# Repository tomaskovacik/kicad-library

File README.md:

schematics parts and PCB footprints for kicad

S3860M-S bluetooth audio module based on OVC3860

XS3886 bluetooth audio module based on OVC3860

MB-CM15113 bluetooth audio module

F-3188 CSR8645 based bluetooth 4.0 module

BLK-MD-SPK-B bluetooth audio module based on OVC3860

68HC05 motorola cpu

SOYO-BT24G03 bluetooth module

aimtec DC-DC convertor AM1D 

F-6888 - BK3254 BT4.0 audio bluetooth module 

Microchip BM20 and BM23 BT modules

F-6188 - BK8000L BT2.0 audio bluetooth module 

MAX809-810 

various 3.5mm jacks

MC33660 

bluepill (stm32F103C)

LM2594

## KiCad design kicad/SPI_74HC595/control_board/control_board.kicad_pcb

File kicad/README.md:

schematics and PCBs made in kicad

- vwcdpic: based on work from www.k9spud.com, remake of PCB, my own tests

arduino_atmega88: single side PCB for arduino based on atmega88 (cheap on ebay ;)

arduino_based_cdc_emulator: PCBs for arduino based CD changer emulator for audi HU

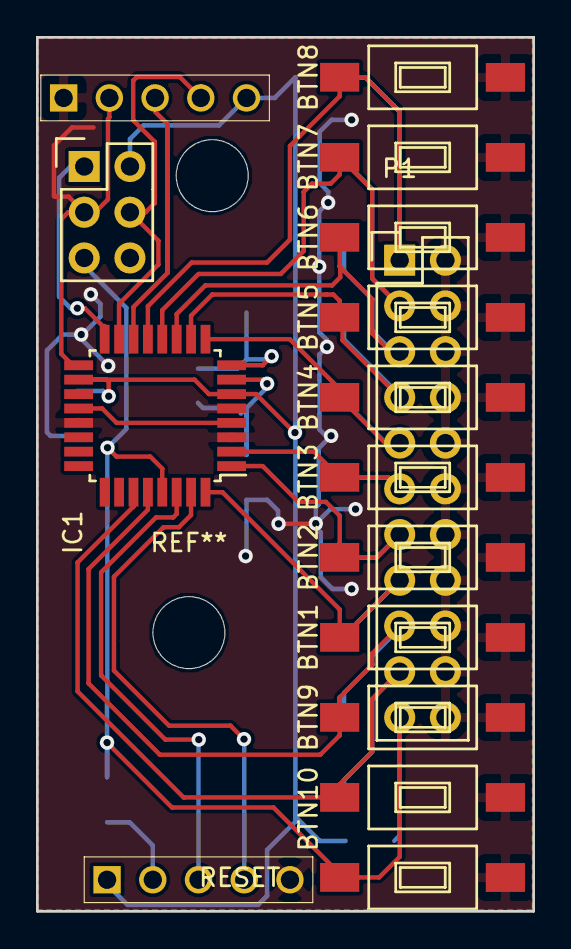
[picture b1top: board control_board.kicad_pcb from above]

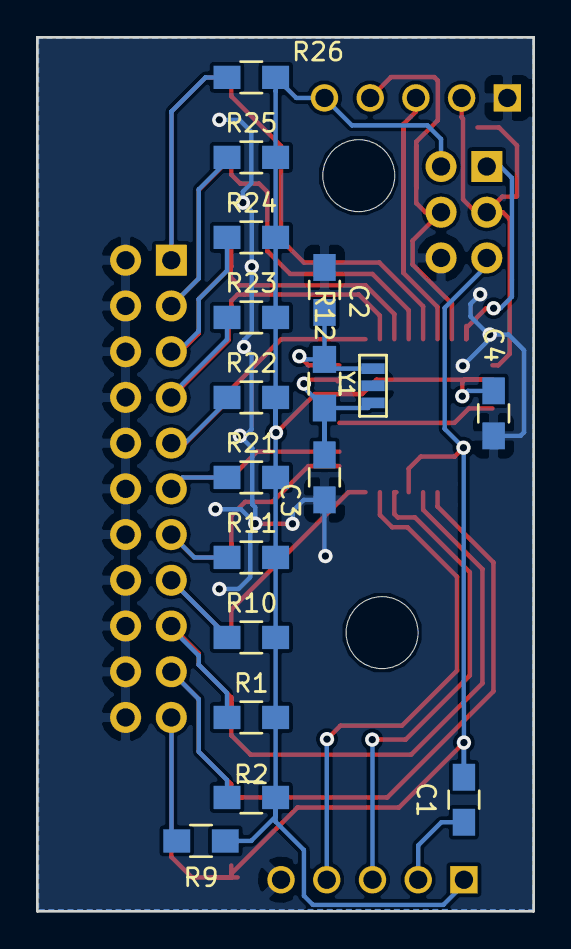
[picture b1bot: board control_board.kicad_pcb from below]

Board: 2 copper layers, 27.6 x 48.6 mm, 33 parts (17 on the bottom side), 22 nets.

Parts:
BTN1, BTN2, BTN3, BTN4, BTN5, BTN6, BTN7, BTN8, BTN9, BTN10: SW_PUSH; SW_SPST_FSMSM
C1, C4: 100n; C_0805_HandSoldering
C2, C3: 22p; C_0805_HandSoldering
IC1: ATMEGA328-A; TQFP-32_7x7mm_Pitch0.8mm
P1: CONN_02X11; Pin_Header_Straight_2x11
P6, P12: CONN_01X05; pin_array_5x1
P10: CONN_02X03; Pin_Header_Straight_2x03
R1, R2, R9, R10, R11, R21, R22, R23, R24, R25, R26: 10k; R_0805_HandSoldering
R12: 1M; R_0805_HandSoldering
RESET: SW_PUSH; SW_SPST_FSMSM
Y1: 16Mhz; MURATA_CSTCE_V53

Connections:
/BTN1: BTN1.1, IC1.32, P1.15, R10.2
/BTN2: BTN2.1, IC1.1, P1.13, R11.2
/BTN3: BTN3.1, IC1.2, P1.11, R21.2
/BTN4: BTN4.1, IC1.9, P1.9, R22.2
/BTN5: BTN5.1, IC1.10, P1.7, R23.2
/BTN6: BTN6.1, IC1.11, P1.5, R24.2
/BTN7: BTN7.1, IC1.12, P1.3, R25.2
/BTN8: BTN8.1, IC1.13, P1.1, R26.2
/BTN9: BTN9.1, IC1.28, P1.17, R1.2
/BTN10: BTN10.1, IC1.27, P1.19, R2.2
/LATCH: IC1.14, P12.3
/MISO: IC1.16, P10.1
/MOSI: IC1.15, P10.4, P12.4
/RESET: C1.2, IC1.29, P1.21, P10.5, R9.2, RESET.1
/RX: IC1.30, P6.3
/SCK: IC1.17, P10.3, P12.2
/TX: IC1.31, P6.4
GND: BTN1.2, BTN2.2, BTN3.2, BTN4.2, BTN5.2, BTN6.2, BTN7.2, BTN8.2, BTN9.2, BTN10.2, C2.2, C3.2, C4.2, IC1.3, IC1.5, IC1.21, P1.2, P1.4, P1.6, P1.8, P1.10, P1.12, P1.14, P1.16, P1.18, P1.20, P1.22, P6.5, P10.6, P12.1, RESET.2, Y1.3
unnamed: C1.1, P6.2
unnamed: C2.1, IC1.8, R12.2, Y1.1
unnamed: C3.1, IC1.7, R12.1, Y1.2
VCC: C4.1, IC1.4, IC1.6, IC1.18, IC1.20, P6.1, P10.2, P12.5, R1.1, R2.1, R9.1, R10.1, R11.1, R21.1, R22.1, R23.1, R24.1, R25.1, R26.1

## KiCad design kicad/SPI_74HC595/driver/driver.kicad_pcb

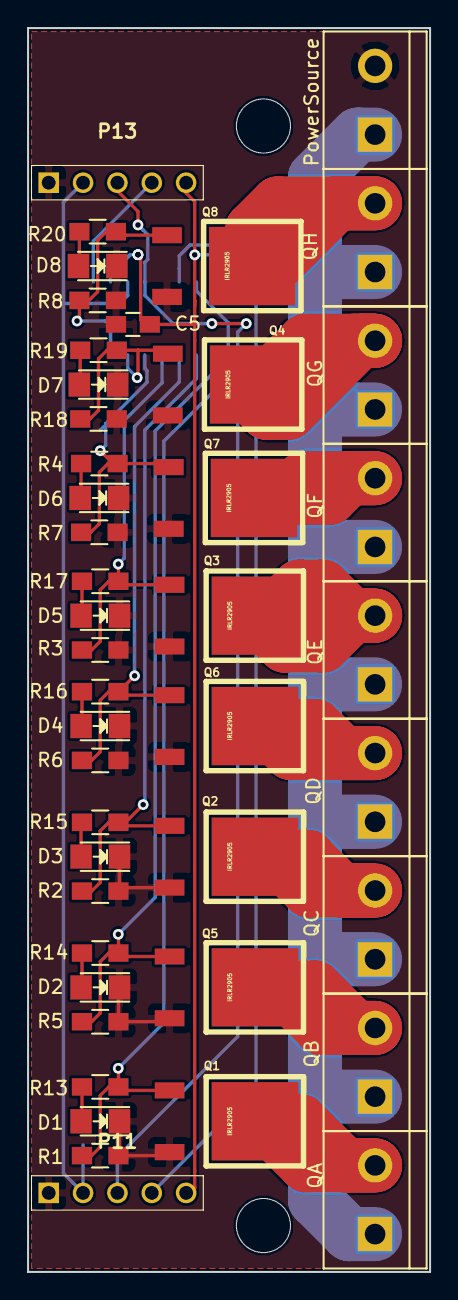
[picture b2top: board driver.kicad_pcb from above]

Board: 2 copper layers, 29.7 x 91.9 mm, 45 parts (1 on the bottom side), 31 nets.

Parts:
C5: 100n; C_0805_HandSoldering
D1, D2, D3, D4, D5, D6, D7, D8: LED; LED_1206
P11, P13: CONN_01X05; pin_array_5x1
PowerSource: CONN_01X02; bornier2
Q1, Q2, Q3, Q4, Q5, Q6, Q7, Q8: IRLR2905; TO-252-3
QA: CONN_01X02; bornier2
QB: CONN_01X02; bornier2
QC: CONN_01X02; bornier2
QD: CONN_01X02; bornier2
QE: CONN_01X02; bornier2
QF: CONN_01X02; bornier2
QG: CONN_01X02; bornier2
QH: CONN_01X02; bornier2
R1, R2, R3, R4, R5, R6, R7, R8: 10k; R_0805_HandSoldering
R13, R14, R15, R16, R17, R18, R19, R20: 470; R_0805_HandSoldering
U1: 74HC595; SOIC-16_3.9x9.9mm_Pitch1.27mm

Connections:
+12V: PowerSource.1, QA.1, QB.1, QC.1, QD.1, QE.1, QF.1, QG.1, QH.1
/LATCH: P11.3, P13.3, U1.12
/MOSI: P11.4, U1.14
/OUT: P13.4, U1.9
/QA: Q1.1, R1.2, R13.2, U1.15
/QB: Q5.1, R5.2, R14.2, U1.1
/QC: Q2.1, R2.2, R15.2, U1.2
/QD: Q6.1, R6.2, R16.2, U1.3
/QE: Q3.1, R3.2, R17.2, U1.4
/QF: Q7.1, R7.2, R18.2, U1.5
/QG: Q4.1, R4.2, R19.2, U1.6
/QH: Q8.1, R8.2, R20.2, U1.7
/SCK: P11.2, P13.2, U1.11
GND: C5.2, D1.1, D2.1, D3.1, D4.1, D5.1, D6.1, D7.1, D8.1, P11.1, P13.1, PowerSource.2, Q1.2, Q2.2, Q3.2, Q4.2, Q5.2, Q6.2, Q7.2, Q8.2, R1.1, R2.1, R3.1, R4.1, R5.1, R6.1, R7.1, R8.1, U1.8, U1.13
unnamed: D1.2, R13.1
unnamed: D2.2, R14.1
unnamed: D3.2, R15.1
unnamed: D4.2, R16.1
unnamed: D5.2, R17.1
unnamed: D6.2, R18.1
unnamed: D7.2, R19.1
unnamed: D8.2, R20.1
unnamed: Q1.3, QA.2
unnamed: Q2.3, QC.2
unnamed: Q3.3, QE.2
unnamed: Q4.3, QG.2
unnamed: Q5.3, QB.2
unnamed: Q6.3, QD.2
unnamed: Q7.3, QF.2
unnamed: Q8.3, QH.2
VCC: C5.1, P11.5, P13.5, U1.10, U1.16

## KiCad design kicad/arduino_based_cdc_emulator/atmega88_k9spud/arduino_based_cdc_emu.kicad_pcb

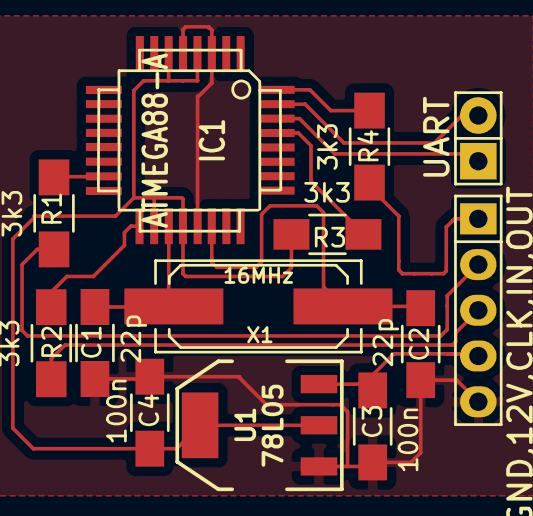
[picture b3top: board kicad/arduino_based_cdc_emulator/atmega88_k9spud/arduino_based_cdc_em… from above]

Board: 2 copper layers, 13 parts (0 on the bottom side), 14 nets.

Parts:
C1, C2: 22p; C_1206_HandSoldering
C3, C4: 100n; C_1206_HandSoldering
GND,12V,CLK,IN,OUT: CONN_5; Pin_Header_Straight_1x05
IC1: ATMEGA88-A; TQFP-32
R1, R2, R3, R4: 3k3; R_1206_HandSoldering
U1: 78L05; SOT-223-REGULATOR
UART: CONN_2; Pin_Header_Straight_1x02
X1: 16MHz; Q_49U3HMS

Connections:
+5V: C4.1, IC1.4, IC1.6, IC1.18, IC1.20, R3.2, U1.VO
+12V: C3.1, GND,12V,CLK,IN,OUT.4, U1.VI
/Clock: GND,12V,CLK,IN,OUT.3, R2.2
/DataIn: GND,12V,CLK,IN,OUT.2, R1.2
/DataOut: GND,12V,CLK,IN,OUT.1, R4.2
GND: C1.1, C2.1, C3.2, C4.2, GND,12V,CLK,IN,OUT.5, IC1.3, IC1.5, IC1.21, U1.GND
unnamed: C1.2, IC1.19, X1.2
unnamed: C2.2, IC1.22, X1.1
unnamed: IC1.15, R1.1
unnamed: IC1.17, R2.1
unnamed: IC1.29, R3.1
unnamed: IC1.32, R4.1
RX: IC1.30, UART.1
TX: IC1.31, UART.2

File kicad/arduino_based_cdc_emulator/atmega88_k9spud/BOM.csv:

"Id";"Designator";"Package";"Quantity";"Designation";"Supplier and ref";
1;"C1,C2";"C_1206_HandSoldering";2;"22p";;;
2;"C3,C4";"C_1206_HandSoldering";2;"100n";;;
3;"IC1";"TQFP-32";1;"ATMEGA88-A";;;
4;"GND,12V,CLK,IN,OUT";"Pin_Header_Straight_1x05";1;"CONN_5";;;
5;"R1,R2,R3,R4";"R_1206_HandSoldering";4;"3k3";;;
6;"U1";"SOT-223-REGULATOR";1;"78L05";;;
7;"X1";"Q_49U3HMS";1;"16MHz";;;
8;"UART";"Pin_Header_Straight_1x02";1;"CONN_2";;;

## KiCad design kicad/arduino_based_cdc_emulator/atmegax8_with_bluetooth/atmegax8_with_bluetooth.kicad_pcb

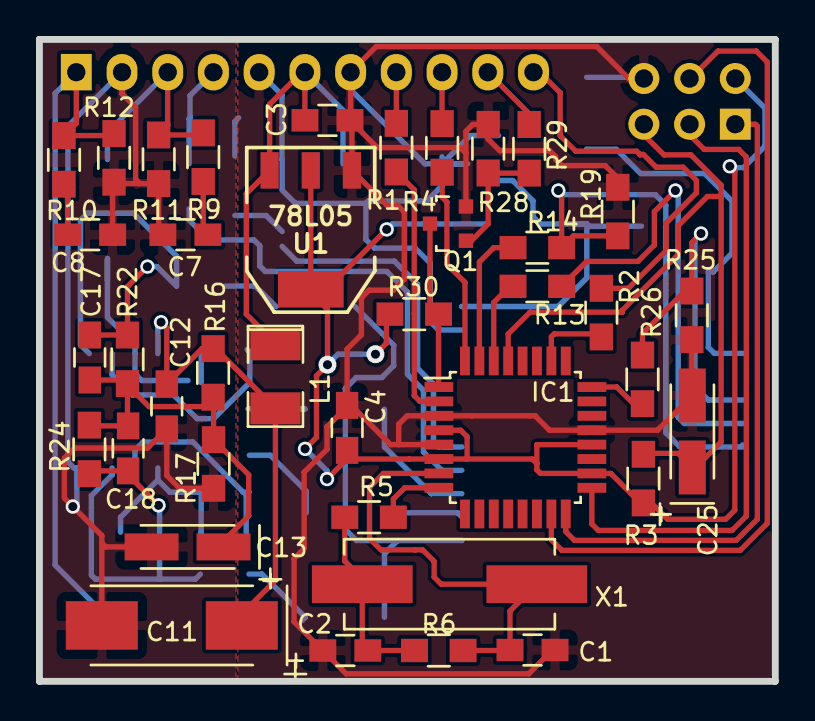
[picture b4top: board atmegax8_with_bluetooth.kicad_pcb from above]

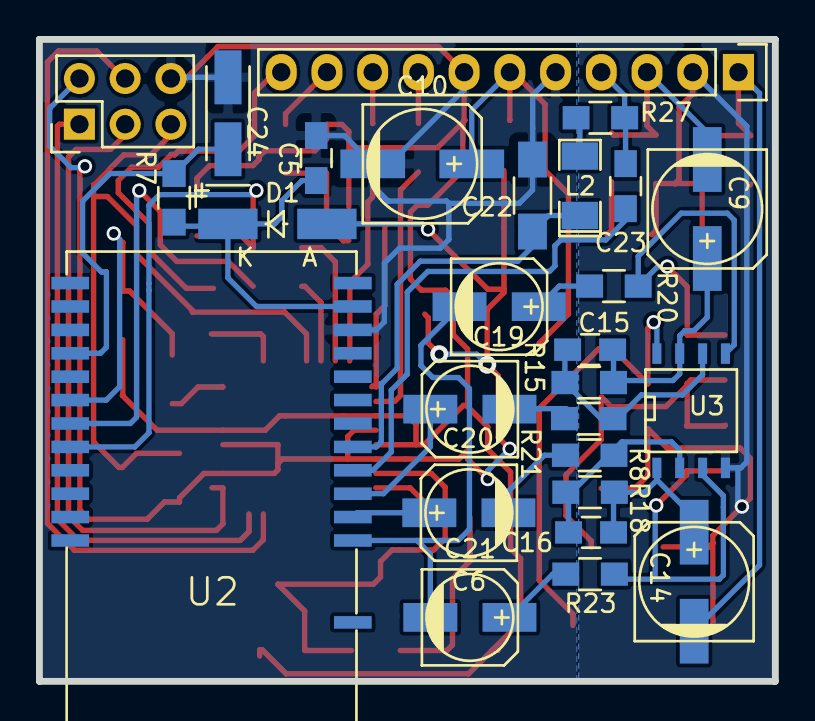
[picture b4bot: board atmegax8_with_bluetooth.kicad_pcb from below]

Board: 2 copper layers, 40.9 x 35.7 mm, 66 parts (27 on the bottom side), 51 nets.

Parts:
C1, C2: 22p; C_0805_HandSoldering
C3, C4, C5, C7, C8, C12: 100n; C_0805_HandSoldering
C6, C19, C20, C21: 10m/16V; c_elec_5x5.8
C9, C14: 47m/25V; c_elec_6.3x5.7
C10: 100m/25V; c_elec_6.3x7.7
C11: 47m/25V; TantalC_SizeD_EIA-7343_HandSoldering
C13: 2m2/16V; TantalC_SizeA_EIA-3216_HandSoldering
C15, C16, C17, C18: 33p; C_0805_HandSoldering
C22: 4u7/10V; C_1206_HandSoldering
C23: 1u/10V; C_0805_HandSoldering
C24: 2u2; TantalC_SizeA_EIA-3216_HandSoldering
C25: 2u1; TantalC_SizeA_EIA-3216_HandSoldering
D1: 1N4148; MiniMELF_Handsoldering
IC1: ATMEGA88-A; TQFP-32_7x7mm_Pitch0.8mm
L1: INDUCTOR; SMD-1210_Pol
L2: 15n; SMD-1206_Pol
P1: CONN_9; Pin_Header_Straight_1x11
P2: SPI; Pin_Header_Straight_2x03
Q1: BC817-40; SOT-23
R1, R2, R3, R4, R7: 3k3; R_0805_HandSoldering
R5: 27; R_0805_HandSoldering
R6: 1M; R_0805_HandSoldering
R8, R20, R21, R23: 22k; R_0805_HandSoldering
R9, R10: 39R; R_0805_HandSoldering
R11, R12, R15, R18, R22, R24, R28: 47k; R_0805_HandSoldering
R13, R14, R26: 330; R_0805_HandSoldering
R16, R17: 100k; R_0805_HandSoldering
R19, R25: 4k7; R_0805_HandSoldering
R27: 2k7(3k3); R_0805_HandSoldering
R29, R30: 10k; R_0805_HandSoldering
U1: 78L05; SOT-223-REGULATOR
U2: S3860M-S
U3: LM358; SOIC-8-N
X1: 16MHz; Crystal_HC49-SD_SMD

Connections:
+5V: C4.1, D1.2, IC1.4, IC1.6, IC1.18, IC1.20, P2.2, R3.2, R30.1, U1.VO
+12C: C11.1, C12.1, L1.2, R16.2, U3.8
+12V: C3.1, C10.1, L1.1, P1.6, U1.VI
+BATT: C5.1, D1.1, R7.2, U2.12
/AOUTL: C14.2, P1.1, R10.2, R12.2
/AOUTR: C9.2, P1.3, R9.2, R11.2
/ARESET: C25.1, IC1.29, P2.5, R3.1
/BTAGND: C19.2, C21.2, U2.2
/BTOUTL: C6.1, U2.3
/BTOUTR: C20.1, U2.4
/BT_ENABLE: IC1.24, R26.2
/BT_RESET: C24.1, R7.1, U2.17
/CDC_ENA_5V: IC1.1, Q1.3, R30.2
/CDC_ENA_12V: P1.10, R29.2
/Clock: IC1.2, R1.2
/DataIn: IC1.26, R2.2
/DataOut: P1.9, R4.2
/MIC: C23.1, U2.5
/MIC_BIAS: C22.1, L2.1, U2.6
/MIC_IN: C23.2, P1.4, R27.1
/MISO: IC1.16, P2.1
/MOSI: IC1.15, P2.4
/SCK: IC1.17, P2.3
/VGND: C13.1, C17.2, C18.2, R16.1, R17.2, R22.1, R24.1
GND: C1.2, C2.2, C3.2, C4.2, C5.2, C10.2, C22.2, C24.2, C25.2, IC1.3, IC1.5, IC1.21, P1.5, P1.7, P2.6, Q1.2, R19.2, R25.2, R28.2, U1.GND, U2.11
GNDA: C7.2, C8.2, C11.2, C12.2, C13.2, P1.2, R11.1, R12.1, R17.1, U3.4
unnamed: C1.1, IC1.7, R6.1, X1.2
unnamed: C2.1, R5.1, R6.2, X1.1
unnamed: C6.2, R8.2
unnamed: C7.1, R9.1
unnamed: C8.1, R10.1
unnamed: C14.1, C16.1, R18.2, U3.1
unnamed: C9.1, C15.1, R15.2, U3.7
unnamed: C15.2, R15.1, R21.1, U3.6
unnamed: C16.2, R8.1, R18.1, U3.2
unnamed: C17.1, R20.2, R22.2, U3.5
unnamed: C18.1, R23.2, R24.2, U3.3
unnamed: C19.1, R20.1
unnamed: C20.2, R21.2
unnamed: C21.1, R23.1
unnamed: IC1.8, R5.2
unnamed: IC1.30, R13.1
unnamed: IC1.31, R14.1
unnamed: IC1.32, R4.1
unnamed: L2.2, R27.2
unnamed: P1.8, R1.1
unnamed: P1.11, R2.1
unnamed: Q1.1, R28.1, R29.1
unnamed: R25.1, R26.1, U2.19
RX: R13.2, U2.20
TX: R14.2, R19.1, U2.21

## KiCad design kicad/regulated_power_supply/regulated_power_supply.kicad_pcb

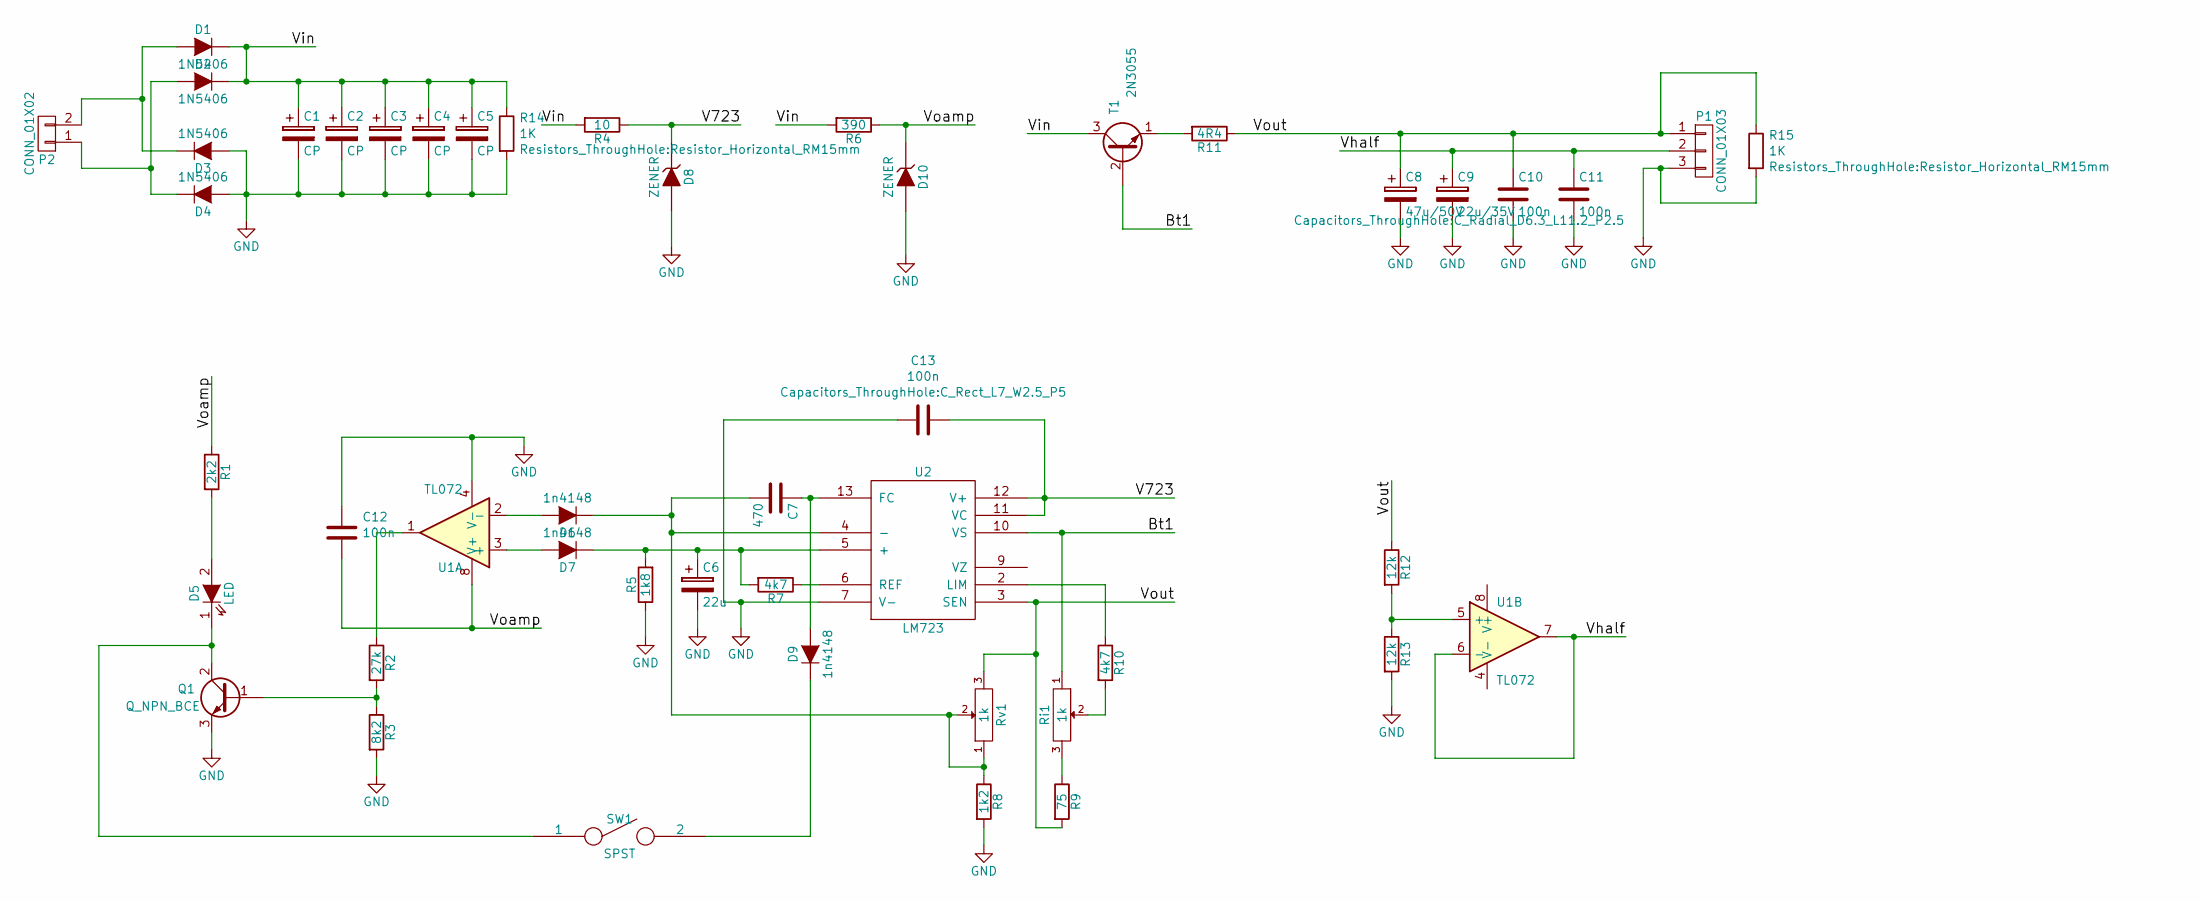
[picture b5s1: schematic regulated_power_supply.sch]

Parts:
C1, C2, C3, C4, C5: CP; C_Radial_D18_L36_P7.5
C6: 22u; C_Radial_D6.3_L11.2_P2.5
C7: 470; C_Rect_L7_W2_P5
C8: 47u/50V; C_Radial_D6.3_L11.2_P2.5
C9: 22u/35V; C_Radial_D6.3_L11.2_P2.5
C10, C11: 100n; C_Rect_L7_W2_P5
C12, C13: 100n; C_Rect_L7_W2.5_P5
D1, D2, D3, D4: 1N5406; Diode_DO-201AD_Horizontal_RM15
D5: LED; LED-5MM
D6, D7, D9: 1n4148; Diode_DO-35_SOD27_Horizontal_RM10
D8, D10: ZENER; Diode_DO-35_SOD27_Horizontal_RM10
P1: CONN_01X03; Pin_Header_Straight_1x03
P2: CONN_01X02; Pin_Header_Straight_1x02
Q1: Q_NPN_BCE; TO-92_Inline_Narrow_Oval
R1: 2k2; Resistor_Horizontal_RM10mm
R2: 27k; Resistor_Horizontal_RM10mm
R3: 8k2; Resistor_Horizontal_RM10mm
R4: 10; Resistor_Horizontal_RM10mm
R5: 1k8; Resistor_Horizontal_RM10mm
R6: 390; Resistor_Horizontal_RM10mm
R7: 4k7; Resistor_Horizontal_RM10mm
R8: 1k2; Resistor_Horizontal_RM10mm
R9: 75; Resistor_Horizontal_RM15mm
R10: 4k7; Resistor_Horizontal_RM15mm
R11: 4R4; Resistor_Horizontal_RM30mm
R12, R13: 12k; Resistor_Horizontal_RM10mm
R14, R15: 1K; Resistor_Horizontal_RM15mm
Ri1: 1k; Pin_Header_Straight_1x03
Rv1: 1k; Pin_Header_Straight_1x03
SW1: SPST; Pin_Header_Straight_1x02
T1: 2N3055; Pin_Header_Straight_1x03
U1: TL072; DIP-8_W7.62mm_LongPads
U2: LM723; DIP-14_W7.62mm_LongPads

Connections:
/Bt1: Ri1.1, T1.2 (B), U2.10 (VS)
/V723: C13.1, D8.1 (K), R4.1, U2.11 (VC), U2.12 (V+)
/Vhalf: C9.1, C11.1, P1.2, U1.6 (-), U1.7
/Vin: C1.1, C2.1, C3.1, C4.1, C5.1, D1.1 (K), D2.1 (K), R4.2, R6.2, R14.1, T1.3 (C)
/Voamp: C12.2, D10.1 (K), R1.1, R6.1, U1.8 (V+)
/Vout: C8.1, C10.1, P1.1, R9.2, R11.1, R12.1, R15.1, Rv1.3, U2.3 (SEN)
GND: C1.2, C2.2, C3.2, C4.2, C5.2, C6.2, C8.2, C9.2, C10.2, C11.2, C12.1, C13.2, D3.2 (A), D4.2 (A), D8.2 (A), D10.2 (A), P1.3, Q1.3 (E), R3.2, R5.1, R8.2, R13.2, R14.2, R15.2, U1.4 (V-), U2.7 (V-)
unnamed: C6.1, D7.1 (K), R5.2, R7.2, U2.5 (+)
unnamed: C7.1, D9.2 (A), U2.13 (FC)
unnamed: C7.2, D6.1 (K), R8.1, Rv1.1, Rv1.2, U2.4 (-)
unnamed: D1.2 (A), D3.1 (K), P2.2
unnamed: D2.2 (A), D4.1 (K), P2.1
unnamed: D5.1 (K), Q1.2 (C), SW1.1
unnamed: D5.2 (A), R1.2
unnamed: D6.2 (A), U1.2 (-)
unnamed: D7.2 (A), U1.3 (+)
unnamed: D9.1 (K), SW1.2
unnamed: Q1.1 (B), R2.2, R3.1
unnamed: R2.1, U1.1
unnamed: R7.1, U2.6 (REF)
unnamed: R9.1, Ri1.3
unnamed: R10.1, U2.2 (LIM)
unnamed: R10.2, Ri1.2
unnamed: R11.2, T1.1 (E)
unnamed: R12.2, R13.1, U1.5 (+)

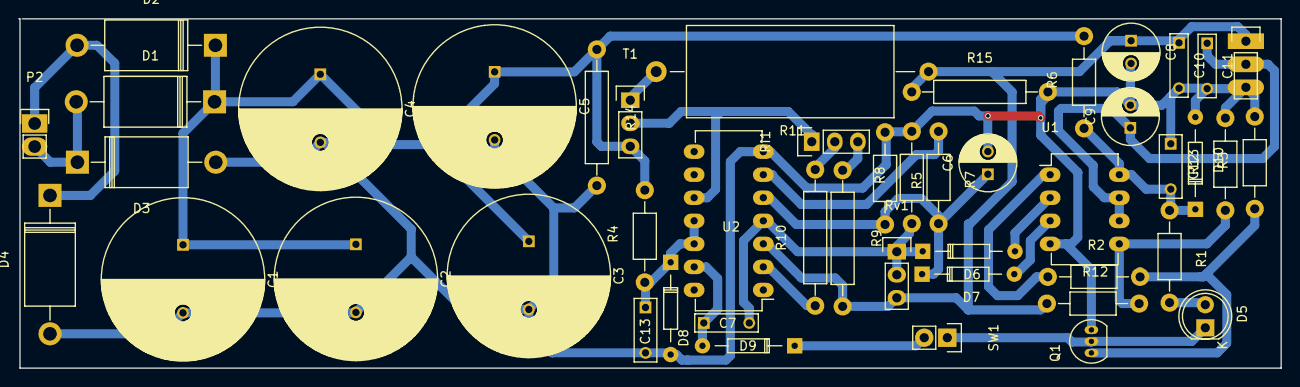
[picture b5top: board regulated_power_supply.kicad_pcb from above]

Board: 2 copper layers, 139.1 x 38.5 mm, 47 parts (0 on the bottom side), 25 nets.

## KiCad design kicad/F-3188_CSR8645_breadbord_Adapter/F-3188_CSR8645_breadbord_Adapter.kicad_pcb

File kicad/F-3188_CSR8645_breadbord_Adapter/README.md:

breadboard adapters for these adapters can be purchase at tindie:

BLK-MD-SPK-B https://www.tindie.com/products/tomaskovacik/breadboard-adapter-for-blk-md-spk-b/

XS3886 / S3860M-s https://www.tindie.com/products/tomaskovacik/breadboard-adapter-for-s3860m-s-sx3868/

SOYO-BT24G03 https://www.tindie.com/products/tomaskovacik/breadboard-adapter-for-soyo-bt24g03-bt-module/

F-3188 https://www.tindie.com/products/tomaskovacik/breadboard-adapter-for-f-3188-csr8645-module/

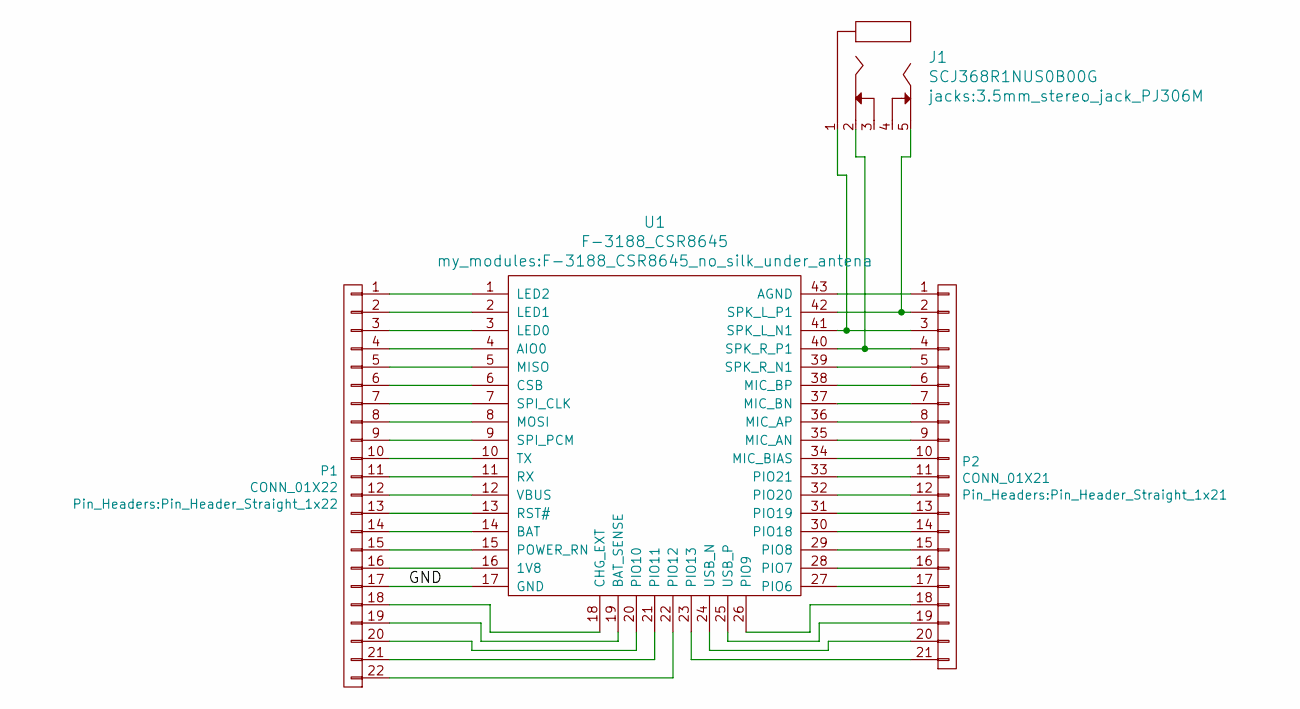
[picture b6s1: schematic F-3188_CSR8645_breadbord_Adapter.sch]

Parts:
J1: SCJ368R1NUS0B00G; 3.5mm_stereo_jack_PJ306M
P1: CONN_01X22; Pin_Header_Straight_1x22
P2: CONN_01X21; Pin_Header_Straight_1x21
U1: F-3188_CSR8645; F-3188_CSR8645_no_silk_under_antena

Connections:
/GND: P1.17, U1.17 (GND)
unnamed: J1.1, P2.3, U1.41 (SPK_L_N1)
unnamed: J1.2, P2.4, U1.40 (SPK_R_P1)
unnamed: J1.5, P2.2, U1.42 (SPK_L_P1)
unnamed: P1.1, U1.1 (LED2)
unnamed: P1.2, U1.2 (LED1)
unnamed: P1.3, U1.3 (LED0)
unnamed: P1.4, U1.4 (AIO0)
unnamed: P1.5, U1.5 (MISO)
unnamed: P1.6, U1.6 (CSB)
unnamed: P1.7, U1.7 (SPI_CLK)
unnamed: P1.8, U1.8 (MOSI)
unnamed: P1.9, U1.9 (SPI_PCM)
unnamed: P1.10, U1.10 (TX)
unnamed: P1.11, U1.11 (RX)
unnamed: P1.12, U1.12 (VBUS)
unnamed: P1.13, U1.13 (RST#)
unnamed: P1.14, U1.14 (BAT)
unnamed: P1.15, U1.15 (POWER_RN)
unnamed: P1.16, U1.16 (1V8)
unnamed: P1.18, U1.18 (CHG_EXT)
unnamed: P1.19, U1.19 (BAT_SENSE)
unnamed: P1.20, U1.20 (PIO10)
unnamed: P1.21, U1.21 (PIO11)
unnamed: P1.22, U1.22 (PIO12)
unnamed: P2.1, U1.43 (AGND)
unnamed: P2.5, U1.39 (SPK_R_N1)
unnamed: P2.6, U1.38 (MIC_BP)
unnamed: P2.7, U1.37 (MIC_BN)
unnamed: P2.8, U1.36 (MIC_AP)
unnamed: P2.9, U1.35 (MIC_AN)
unnamed: P2.10, U1.34 (MIC_BIAS)
unnamed: P2.11, U1.33 (PIO21)
unnamed: P2.12, U1.32 (PIO20)
unnamed: P2.13, U1.31 (PIO19)
unnamed: P2.14, U1.30 (PIO18)
unnamed: P2.15, U1.29 (PIO8)
unnamed: P2.16, U1.28 (PIO7)
unnamed: P2.17, U1.27 (PIO6)
unnamed: P2.18, U1.26 (PIO9)
unnamed: P2.19, U1.25 (USB_P)
unnamed: P2.20, U1.24 (USB_N)
unnamed: P2.21, U1.23 (PIO13)

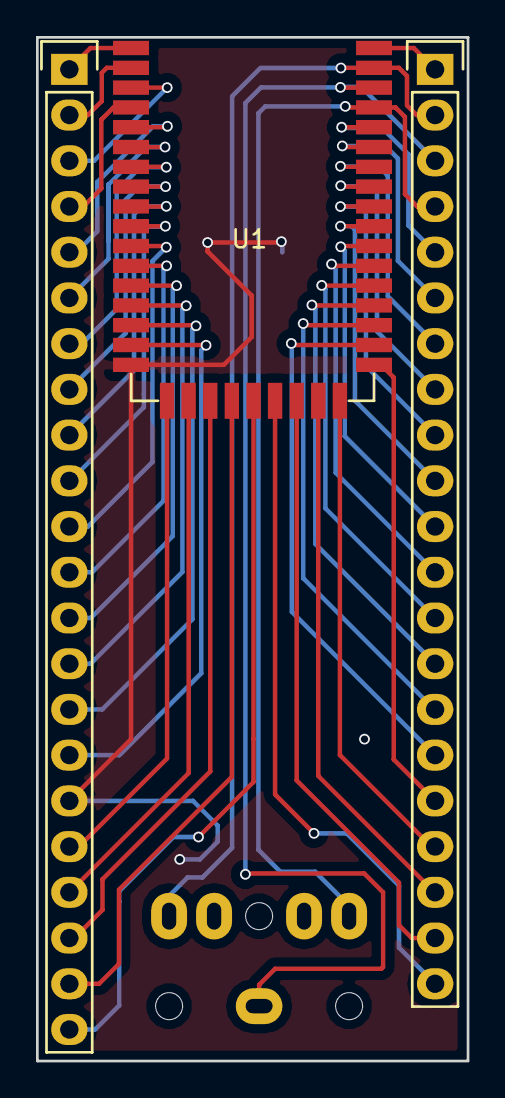
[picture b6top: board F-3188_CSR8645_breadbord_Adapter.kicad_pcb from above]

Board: 2 copper layers, 23.9 x 56.9 mm, 4 parts (1 on the bottom side), 43 nets.

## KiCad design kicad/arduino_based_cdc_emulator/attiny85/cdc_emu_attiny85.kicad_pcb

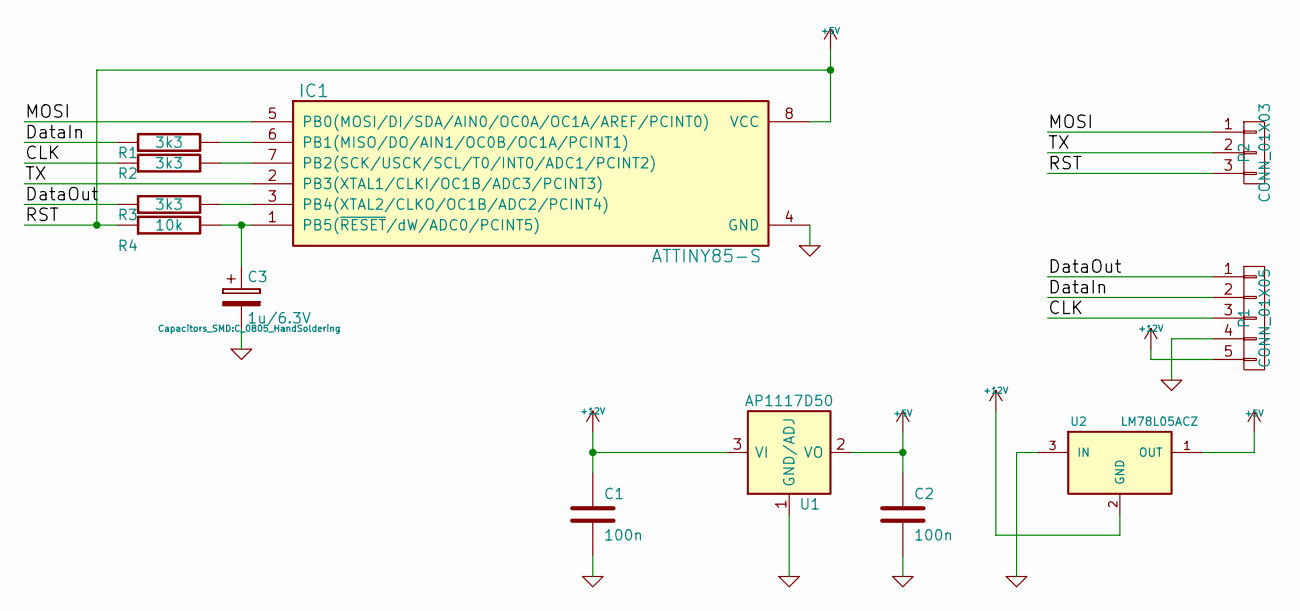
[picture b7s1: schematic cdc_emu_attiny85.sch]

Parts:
C1, C2: 100n; C_0805_HandSoldering
C3: 1u/6.3V; C_0805_HandSoldering
IC1: ATTINY85-S; SOIC-8-N_wide_pads
P1: CONN_01X05; Pin_Header_Straight_1x05
P2: CONN_01X03; Pin_Header_Straight_1x03
R1, R2, R3: 3k3; R_0805_HandSoldering
R4: 10k; R_0805_HandSoldering
U1: AP1117D50; SOT-223
U2: LM78L05ACZ; SOT-23

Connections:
+5V: C2.1, IC1.8 (VCC), P2.3, R4.1, U1.2 (VO), U1.4, U2.1 (OUT)
+12V: C1.1, P1.5, U1.3 (VI), U2.2 (GND)
/CLK: P1.3, R2.1
/DataIn: P1.2, R1.1
/DataOut: P1.1, R3.1
/MOSI: IC1.5 (PB0(MOSI/DI/SDA/AIN0/OC0A/OC1A/AREF/PCI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), P2.1
/TX: IC1.2 (PB3(XTAL1/CLKI/OC1B/ADC3/PCINT3)), P2.2
GND: C1.2, C2.2, C3.2, IC1.4 (GND), P1.4, U1.1 (GND/ADJ), U2.3 (IN)
unnamed: C3.1, IC1.1 (PB5(~RESET~/dW/ADC0/PCINT5)), R4.2
unnamed: IC1.3 (PB4(XTAL2/CLKO/OC1B/ADC2/PCINT4)), R3.2
unnamed: IC1.6 (PB1(MISO/DO/AIN1/OC0B/OC1A/PCINT1)), R1.2
unnamed: IC1.7 (PB2(SCK/USCK/SCL/T0/INT0/ADC1/PCINT2)), R2.2

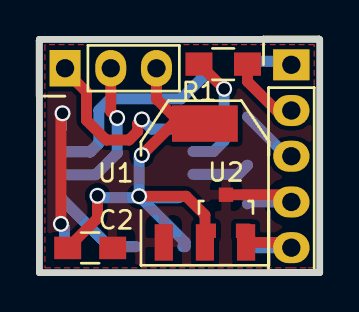
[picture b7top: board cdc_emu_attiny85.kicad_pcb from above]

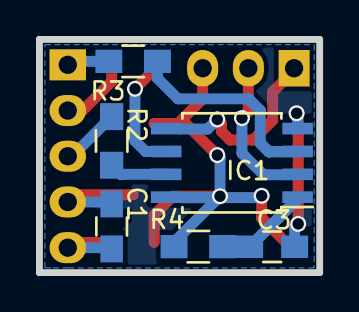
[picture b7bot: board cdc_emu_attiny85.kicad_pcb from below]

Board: 2 copper layers, 15.6 x 13.0 mm, 12 parts (6 on the bottom side), 12 nets.

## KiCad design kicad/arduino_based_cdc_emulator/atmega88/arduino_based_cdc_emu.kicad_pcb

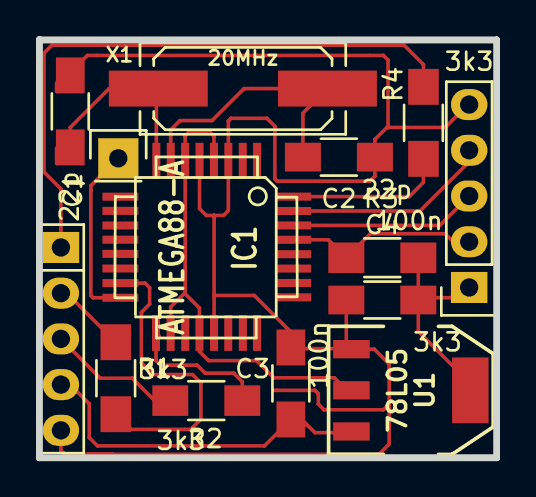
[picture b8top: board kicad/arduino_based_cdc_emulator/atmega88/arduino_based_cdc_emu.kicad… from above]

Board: 2 copper layers, 25.4 x 23.2 mm, 14 parts (0 on the bottom side), 15 nets.

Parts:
C1, C2: 22p; C_1206_HandSoldering
C3, C4: 100n; C_1206_HandSoldering
IC1: ATMEGA88-A; TQFP-32
P1: CONN_1; Pin_Header_Straight_1x05
P2: CONN_2; Pin_Header_Straight_1x05
P3: CONN_3; Pin_Header_Straight_1x01
R1, R2, R3, R4: 3k3; R_1206_HandSoldering
U1: 78L05; SOT-223-REGULATOR
X1: 20MHz; Q_49U3HMS

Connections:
+5V: C4.1, IC1.4, IC1.6, IC1.18, IC1.20, P2.1, R3.2, U1.VO
+12V: C3.1, P1.4, U1.VI
/Clock: P1.3, R2.2
/DataIn: P1.2, R1.2
/DataOut: P1.1, R4.2
/MISO: IC1.16, P3.1
/RESET: IC1.29, P2.2, R3.1
GND: C1.1, C2.1, C3.2, C4.2, IC1.3, IC1.5, IC1.21, P1.5, P2.5, U1.GND
unnamed: C1.2, IC1.8, X1.2
unnamed: C2.2, IC1.7, X1.1
unnamed: IC1.15, R1.1
unnamed: IC1.17, R2.1
unnamed: IC1.32, R4.1
RX: IC1.30, P2.3
TX: IC1.31, P2.4

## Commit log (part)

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2015-08-14 change to 0805 size
2015-08-25 revert to version 3 based
2015-08-25 deleted obsolete files
2015-09-06 bluetooth breakout adapter board for btm-68D module
2015-10-07 cleanup
2015-10-07 kicad upgrade files
2015-10-07 rename pic_emulator_smd_no_audio vwcdpic
2015-10-07 PICTURES OF ardpicprog shield
2015-10-07 THT version for easy DIY
2015-10-09 remake_pcb/*
2015-10-09 78L05 int SOT23 package as alternative to AM1117
2015-10-09 moved to new repo vwcdpic https://github.com/tomaskovacik/vwcdpic/tree/master/
2015-11-18 3d rendered pictures
2015-11-18 through hole version
2015-11-18 double sided smd load version 0805 R,C components
2015-11-18 new kicad version components in schematics
2015-11-18 4066 powered from battery to have lower switchedON resistance then on 5V
2015-11-18 board for attiny version vwcdavr smd
2015-11-19 SCJ-0354-5PU 3.5mm stereo jack without screee on silkscreen
2015-11-19 XS3868 witout antene part of silkscreen
2015-11-19 tantal C with just 1 plus symbol ...
2015-11-19 BLK-MD-SPK-B witout antene part of silkscreen
2015-11-19 XS3868 schematics
2015-11-19 no silkscreen parts
2015-11-19 ignore bak bck cached.lib files ...
2015-11-19 pcb update
2015-11-19 pcb, really need rework.
2015-11-19 need rework, changed kicad.....
2015-11-19 audio source board update
2015-11-19 deleted bak files
2015-11-23 3dviews, schematics pics
2015-11-23 these do not need on github
2015-11-23 schematics with new kicad version
2015-11-23 background on exported schematics
2015-11-23 deleted unneeded files from github
2015-11-23 pics in readme
2015-12-07 silkscreen module update
2015-12-07 update parts for new version of kicad
2015-12-07 initial commit, car interior "sulfid" LED 42m
2015-12-07 typo, rename
2015-12-07 MSOP breadboard adapter
2015-12-07 SOIC16 breadboard adapter
2015-12-07 SOIC28 breadboard adapter
2015-12-07 SC70 breadboard adapter
2015-12-07 rename bt_breakout_adapter_xs3868 to XS3868_breadboard_adapter
2015-12-07 rename sc70_breadboard_adapter to SC70_breadboard_adapter
2015-12-07 rename bluetooth_breadboard_adapter to blk-md-spk-b_breadboard_adapter
2015-12-07 delte after rename
2015-12-08 readme init
2015-12-08 SOYO-BT24G03 bluetooth audio module, init commit
2015-12-08 change pin orientation from T to U
2015-12-17 wrong pin number
2015-12-18 revork board to be only 25.4mm wide, for fit inside bread board and leave space for cables on both sides
2015-12-18 pictures of finished adapter
2015-12-18 sot23-6 breadboard adapter
2015-12-18 2more SMT jack modules
2015-12-18 LM723 based revork of my old power supply
2015-12-18 update pcb,jack, layout
2015-12-18 gitignore
2015-12-18 rename bt_breakout_adapter_btm-68D->MB-CM15113-btm-68D_breakout_adapter
2015-12-18 work in progress, pcb design
2016-01-05 raname XS3860 to XS 3868
2016-01-05 rename xs3860 to xs3868
2016-01-07 rename XS3868 to S3860M-S
2016-01-07 delete
2016-01-19 arduino based cdc for VAG with bluetooth
2016-01-19 x3860m-s module
2016-01-19 pics of prototypes
2016-01-19 module update
2016-01-20 PCB layout work
2016-01-23 tool to configure ovc3860 based modules
2016-01-23 how to us tool to configure ovc3860 based modules OVC3860_revd_config_tool.exe
2016-01-25 readme
2016-01-26 readme update
2016-02-22 updated version
2016-02-22 url fix
2016-02-22 schematics udpate
2016-03-03 new pics, readme
2016-03-08 kicad module for CSR8645 bluetooth module
2016-03-10 0805 resistors as jumpers for selecting module
2016-03-10 fix 78L05 pinout, 5V connection from U1
2016-03-10 dumps of ovc3860 from diferent modules, with diferent configuration
2016-03-10 layout update
2016-03-10 3.5mm_stereo_jack_PJ3020B_no_up_silkscreen
2016-03-10 differencial audio preamplifier LM358 for bluetooth modules
2016-03-10 link to video
2016-03-10 update BLK-MD-SPK-B library
2016-03-10 update to 3.5mm_stereo_jack_PJ3020B module
2016-03-10 work in progress..
2016-03-10 just update to rescue library, why kicad is doing this???
2016-03-10 finished? I gues yes, board for vwcdavr emulator with bluetooth
2016-03-10 fix name
2016-03-10 wrong name
2016-03-10 change jumper resistors to select module from 0402 to 0805, corect name for jack is PJ320B
2016-03-10 pictures of made board
2016-03-14 assambly plan
2016-03-14 update for GND/VBUCK diffrence betwen S3860M-S and XS3868 module, using sMD jumpers for selection betwen modules
2016-03-14 pics
2016-03-14 right package for attiny85
2016-03-14 assambly plan in svg/png
2016-03-16 kicad library for F-3188 BLE bluetooth 4.0 module based on CSR8645
2016-03-16 sort of datasheet for F-3188 ble bluetooth 4.0 ad2p module based on CSR8645 chip
2016-03-16 kicad module for F-3188 BLE bluetooth 4.0 module based on CSR8645
2016-03-16 kicad module for murata CSTCE V53 SMD resonator
2016-03-16 breadboard adapter for F-3188 BLE bluetooth 4.0 module based on CSR8645
2016-03-16 renamed to F-3188_CSR8645*
2016-03-21 change LM358 to ne5532, same pics from net with actual module, sold by elecfreeks
2016-04-01 white bg
2016-04-01 moved to pics dir
2016-08-31 removed pledgie
2016-09-26 pics of prototype, fist run of PCBs
2016-09-26 udpates
2016-09-26 AGND pin
2016-09-26 udapte
2016-09-26 AGND pin separated from GND
2016-09-26 remove backup file
2016-09-26 updates, I do not remember what I changed ....
2016-10-28 fix values
2016-11-14 assamble plan, BOM
2017-01-25 readme udpate
2017-02-22 Bill of materials, assamble planes for various projects
2017-02-22 pics of finished board
2017-02-22 datasheet udpate, new modules
2017-03-09 removed fcked board design
2017-07-07 SPI 74HC595 driver plus control board project
2017-07-07 crystal footprint fix
2017-09-08 moved library folder to separate repository
2017-09-08 rename CSR8645_bluetooth -> F-3188_CSR8645_bluetooth
2017-09-08 F-6188 datasheet
2017-09-08 F-6888 datasheet
2017-09-08 schematics kicad part f-6888
2017-09-08 kicad footprint for F-6888 module
2017-09-08 udpate f-6888 lib
2017-09-08 f-3188 datasheet rename
2017-09-11 Technical-Description-2510161.pdf was for F-6288 module
2017-09-11 BK8000L datasheet printed from Technical-Description-2510161.pdf, wich was part of this repo before
2017-09-11 rename
2017-10-25 new info
2017-11-07 flash content
2017-11-07 flashrom patch for support spiflash used on BK8000L module
2017-11-07 ghex picture of change name
2018-02-11 BM20 and BM23 schematics symbosl for kicad
2018-02-11 xs3868 schematic symbol for kicad
2018-02-11 BM20 BM23 kicad footprint modules
2018-02-11 F-6188 BK8000L kicad footprint module
2018-02-11 duplicate
2018-02-11 desc. update
2018-02-11 various updates
2018-02-12 F-6188 BK8000L based bluetooth module
2018-02-12 F-6188 BK8000L based bluetooth module - documents
2018-02-12 F-3188 CSR8645 based bluetooth module - documents
2018-02-12 F-6888 bk3254 based bluetooth module - documents
2018-02-12 rev E config tool for ovc3860 based moduels
2018-02-12 lib update
2018-02-12 detele of datasheet/BLK-MD-SPK-B_AT_Commands_OVC3860_List.pdf
2018-02-12 modified exe? o_O
2018-02-20 remove large file
2018-02-20 empty
2018-03-11 readme init, revwrite of datasheet, test and so on
2018-03-11 updated print from archive.org
2018-03-11 schematics symbol of BK8000L symbol in svg
2018-03-11 replace cvg with png, smaller size
2018-03-11 F-6188_schematics_symbol.png update position of module in picture
2018-03-11 pcb module picture
2018-03-11 update modules, parts which are typicaly out of PCB are now in user drw layer
2018-03-11 BM20 and BM32 schematics lib for kicad update
2018-03-11 F-6188 kicad schematics update
2018-03-11 F-6888 kicad schematics update
2018-03-11 change layer of moduler outline which is typicaly outside of PCB to userdrawing layer from silckscreen
2018-03-11 update of modules
2018-03-11 pdf for stereo jack type: PJ-327A
2018-03-11 ovc3860 configuration tool revision E
2018-03-11 product information from ebay seller
2018-03-11 update, antena part of module is now in user drawing layer
2018-03-12 move jack pdf to jack.pretty directory
2018-03-19 bins from BK8000L google group
2018-03-19 update jack PJ320B pinout
2018-03-19 update jack PJ320B library
2018-03-19 BK8000L lib update
2018-03-19 update jack PJ_J327A library
2018-03-19 3x6x2.5mm tactile switch
2018-03-19 move bluetooth modules to bluetooth.pretty
2018-03-19 f-6888 lib rename to F-6888
2018-03-19 F-6188 PCB module remove
2018-03-19 datasheet folder cleanup
2018-04-23 moved pins 0.2mm to back, based on real part in hand
2018-07-20 link to library
2018-07-30 remove tested at commands, which did not works
2018-08-20 tideup folders
2018-08-20 update url to repository with arduino library in readme
2018-09-10 mode jacks to jack library
2018-09-10 fix formating
2018-09-10 various PSKEY dump files
2018-09-10 new url to datasheet of FT25H04.pdf
2018-09-10 files
2018-10-02 pskeydump which enable call function on BLK module
2018-10-04 K02 datasheets
2018-11-07 datasheet mirror from https://oss.aliyuncs.com/netmarket/29bc7cac-8266-45bf-b2b0-f152227ba546.pdf
2018-11-07 new files
2018-11-07 deleted
2018-11-07 version pictures
2018-11-08 init rc files for exe files
2018-11-08 english version
2018-11-09 multileng 3254_ToolKit2.6.exe
2018-11-09 english RC for 3254_ToolKit2.6.exe
2018-11-09 Chinas RC for 3254_ToolKit2.6.exe
2018-11-09 multilang Beken_ProgramVer4.rc
2018-11-09 chinas rc for Beken_ProgramVer4.exe
2018-11-09 english rc for Beken_ProgramVer4.exe
2018-11-09 mode multilingual traslated executables...
2018-11-10 translate hardcoded strings
2018-11-17 new translations
2018-11-17 deleted BK3254_toolkit_V2.6.png
2018-11-17 rename Beken_ProgramVer4.exe
2018-12-22 fix dimensions
2018-12-22 modules update
2018-12-22 library update
2018-12-22 remove temporary files
2018-12-22 remove temporary files./3254_ToolKit2.6.exe.1
2019-01-30 atmega324PB
2019-01-30 remove atmega324pb, it is in github lib on github
2019-01-30 Revert "remove atmega324pb, it is in github lib on github" cose kicad part sux ... it has only main pin names (PAx,PBx..) none of alternate functions
    This reverts commit a33424b53c2e1e08e85b4376b71125e0041925a5.
2020-04-16 microchip bm64 bt module kicadl library
2020-04-16 microchip bm64 bt module kicad module/footprint
2020-04-16 microchip BM71 bt module kicadl library
2020-04-16 HM-10 module kicad symbol
2020-04-16 HM-10 kicad footprint
2020-04-16 ad datasheet path
2020-04-16 BM71 schematics symbol for kicad
2020-04-16 rename to correct name
2020-04-22 working config, autopairing still does not works:/
2020-04-22 notes
2020-06-03 BM23 update
2020-06-03 3d model NA series fujitsu/takamisawa relays
2020-06-03 NA series relays
2020-06-25 my firmware with serial support enabled
2020-06-25 eeprom upgrade sketch
2020-07-16 moved to lfs
2020-07-16 psk from net
2020-07-16 change mode
2020-07-16 move to lfs
2020-07-16 update mode
2020-07-16 moving to lfs
2020-07-22 readme with links
2020-07-22 add EAN PIN
2020-07-22 udpate
2020-07-22 BM20, BM62 support
2020-07-22 eeprom patch with serial enabled
2020-07-22 my modules config
2020-07-22 eeprom patch with AUDI_BM20.txt
2020-07-22 eeprom patch fro 2.1.3 firmware for BM62
2020-07-23 eeprom patch configuration, for DSP2.1.3 firmware
2021-01-01 bk3266 translated datasheet from HYTlibrary/datasheet/BK3266/
2021-01-01 bk8002 translated datasheet from HYT
2021-01-30 serial protocol for BK3266SR
2021-04-19 Update notes.md
    DI0=>DT0
2021-04-20 my config files for bm64
2021-05-07 my notes
2021-05-10 PCB module for BM6x
2021-05-10 BM83 PCB module
2021-05-10 schematics symbol for bm83
2021-05-10 automotive relays footprints
2021-05-10 wider pins
2021-08-26 my_flash_working_serial_audio_phone.bin
